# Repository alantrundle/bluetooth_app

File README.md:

# Project
* SwiftUI × CoreBluetooth Sample Code ...
# Built With
* CoreBluetooth
# Versioning
* target -> iOS 14.1 ↑
* Xcode --12.4
* Swift -- 5.3
* SwiftUI -- 2.0
# Authors
* Alan Trundle

# bluetooth_app
#

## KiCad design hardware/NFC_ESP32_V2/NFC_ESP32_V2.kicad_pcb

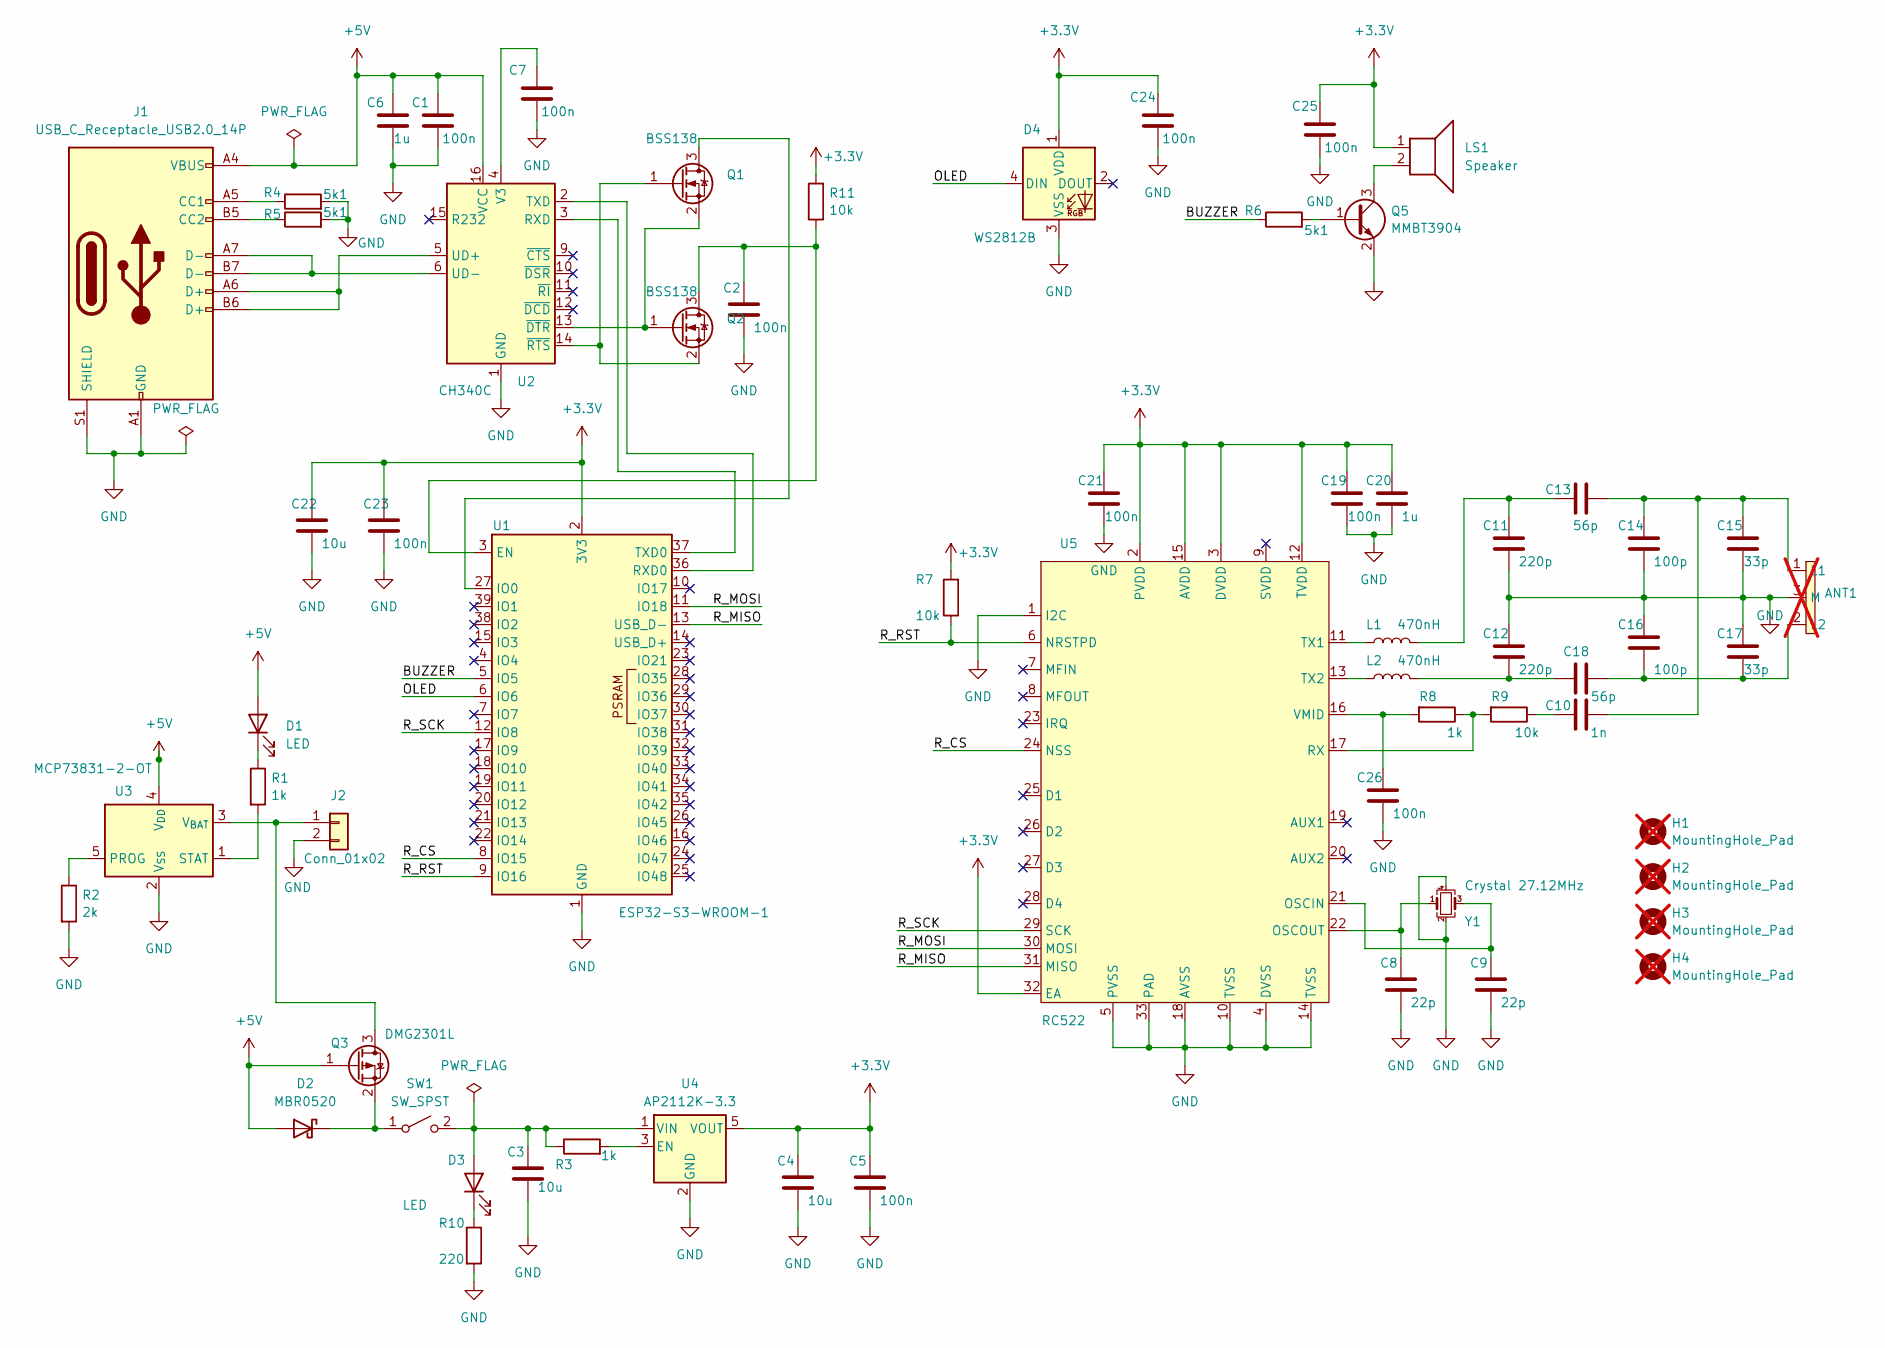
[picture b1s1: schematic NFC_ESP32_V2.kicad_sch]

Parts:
ANT1: RFID_Antenna2; not fitted
C1, C2, C5, C7, C19, C21, C23, C24, C25, C26: 100n; C_0603_1608Metric; LCSC C5137636
C3, C4, C22: 10u; C_0805_2012Metric_Pad1.18x1.45mm_HandSolder; LCSC C15850
C6, C20: 1u; C_0603_1608Metric; LCSC C1592
C8, C9: 22p; C_0603_1608Metric; LCSC C105620
C10: 1n; C_0603_1608Metric; LCSC C1523
C11, C12: 220p; C_0603_1608Metric
C13, C18: 56p; C_0603_1608Metric
C14, C16: 100p; C_0603_1608Metric
C15, C17: 33p; C_0603_1608Metric
D1, D3: LED; LED_0603_1608Metric
D2: MBR0520; D_SOD-123; LCSC C77335
D4: WS2812B; LED_WS2812B_PLCC4_5.0x5.0mm_P3.2mm; LCSC C114586
H1, H2, H3, H4: MountingHole_Pad; MountingHole_2.2mm_M2; not fitted
J1: USB_C_Receptacle_USB2.0_14P; USB_C_Receptacle_JAE_DX07S016JA1R1500; LCSC C3197885
J2: Conn_01x02; JST_ZH_S2B-ZR-SM4A-TF_1x02-1MP_P1.50mm_Horizontal; LCSC C20422588
L1, L2: 470nH; L_0603_1608Metric_Pad1.05x0.95mm_HandSolder; LCSC C280285
LS1: Speaker; Buzzer_TDK_PS1240P02BT_D12.2mm_H6.5mm; LCSC C76873
Q1, Q2: BSS138; SOT-23; LCSC C40912
Q3: DMG2301L; SOT-23; LCSC C7472914
Q5: MMBT3904; SOT-23; LCSC C2923360
R1, R3, R8: 1k; R_0603_1608Metric
R2: 2k; R_0603_1608Metric
R4, R5, R6: 5k1; R_0603_1608Metric
R7, R9, R11: 10k; R_0603_1608Metric
R10: 220; R_0603_1608Metric
SW1: SW_SPST; SW_Slide_SPDT_Angled_CK_OS102011MA1Q; LCSC C226259
U1: ESP32-S3-WROOM-1
U2: CH340C; SOIC-16_3.9x9.9mm_P1.27mm; LCSC C84681
U3: MCP73831-2-OT; SOT-23-5; LCSC C424093
U4: AP2112K-3.3; SOT-23-5; LCSC C51118
U5: RC522; HVQFN-32-1EP_5x5mm_P0.5mm_EP3.1x3.1mm_ThermalVias; LCSC C41361612
Y1: Crystal 27.12MHz; Crystal_SMD_3225-4Pin_3.2x2.5mm; LCSC C164053

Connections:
+3.3V: C4.1, C5.1, C19.1, C20.1, C21.1, C22.1, C23.1, C24.1, C25.1, D4.1 (VDD), LS1.1, R7.2, R11.2, U1.2 (3V3), U4.5 (VOUT), U5.2 (PVDD), U5.3 (DVDD), U5.12 (TVDD), U5.15 (AVDD), U5.32 (EA)
+5V: C1.1, C6.1, D1.2 (A), D2.2 (A), J1.A4 (VBUS), J1.A9 (VBUS), J1.B4 (VBUS), J1.B9 (VBUS), Q3.1 (G), U2.16 (VCC), U3.4 (V_{DD})
/BUZZER: R6.1, U1.5 (IO5)
/OLED: D4.4 (DIN), U1.6 (IO6)
/R_CS: U1.8 (IO15), U5.24 (NSS)
/R_MISO: U1.13 (USB_D-), U5.31 (MISO)
/R_MOSI: U1.11 (IO18), U5.30 (MOSI)
/R_RST: R7.1, U1.9 (IO16), U5.6 (NRSTPD)
/R_SCK: U1.12 (IO8), U5.29 (SCK)
GND: ANT1.3 (M), C1.2, C2.2, C3.2, C4.2, C5.2, C6.2, C7.2, C8.2, C9.2, C11.2, C12.1, C14.2, C15.2, C16.1, C17.1, C19.2, C20.2, C21.2, C22.2, C23.2, C24.2, C25.2, C26.2, D4.3 (VSS), J1.A1 (GND), J1.A12 (GND), J1.B1 (GND), J1.B12 (GND), J1.S1 (SHIELD), J2.2, Q5.2 (E), R2.2, R4.2, R5.2, R10.2, U1.1 (GND), U1.40 (GND), U1.41 (GND), U2.1 (GND), U3.2 (V_{SS}), U4.2 (GND), U5.1 (I2C), U5.4 (DVSS), U5.5 (PVSS), U5.10 (TVSS), U5.14 (TVSS), U5.18 (AVSS), U5.33 (PAD), Y1.2, Y1.4
unnamed: ANT1.1 (L1), C10.2, C13.2, C14.1, C15.1
unnamed: ANT1.2 (L2), C16.2, C17.2, C18.2
unnamed: C10.1, R9.1
unnamed: C11.1, C13.1, L1.2
unnamed: C12.2, C18.1, L2.2
unnamed: D1.1 (K), R1.1
unnamed: D2.1 (K), Q3.2 (S), SW1.1 (A)
unnamed: C3.1, D3.2 (A), R3.1, SW1.2 (B), U4.1 (VIN)
unnamed: D3.1 (K), R10.1
unnamed: J1.A5 (CC1), R4.1
unnamed: J1.B5 (CC2), R5.1
unnamed: J2.1, Q3.3 (D), U3.3 (V_{BAT})
unnamed: Q1.3 (D), U1.27 (IO0)
unnamed: Q1.1 (G), Q2.2 (S), U2.14 (~RTS)
unnamed: Q1.2 (S), Q2.1 (G), U2.13 (~DTR)
unnamed: C2.1, Q2.3 (D), R11.1, U1.3 (EN)
unnamed: Q5.1 (B), R6.2
unnamed: LS1.2, Q5.3 (C)
unnamed: U1.36 (RXD0), U2.2 (TXD)
unnamed: U1.37 (TXD0), U2.3 (RXD)
unnamed: J1.A6 (D+), J1.B6 (D+), U2.5 (UD+)
unnamed: J1.A7 (D-), J1.B7 (D-), U2.6 (UD-)
unnamed: C7.1, U2.4 (V3)
unnamed: R2.1, U3.5 (PROG)
unnamed: R1.2, U3.1 (STAT)
unnamed: R3.2, U4.3 (EN)
unnamed: C9.1, U5.21 (OSCIN), Y1.3
unnamed: C8.1, U5.22 (OSCOUT), Y1.1
unnamed: R8.1, R9.2, U5.17 (RX)
unnamed: L1.1, U5.11 (TX1)
unnamed: L2.1, U5.13 (TX2)
unnamed: C26.1, R8.2, U5.16 (VMID)

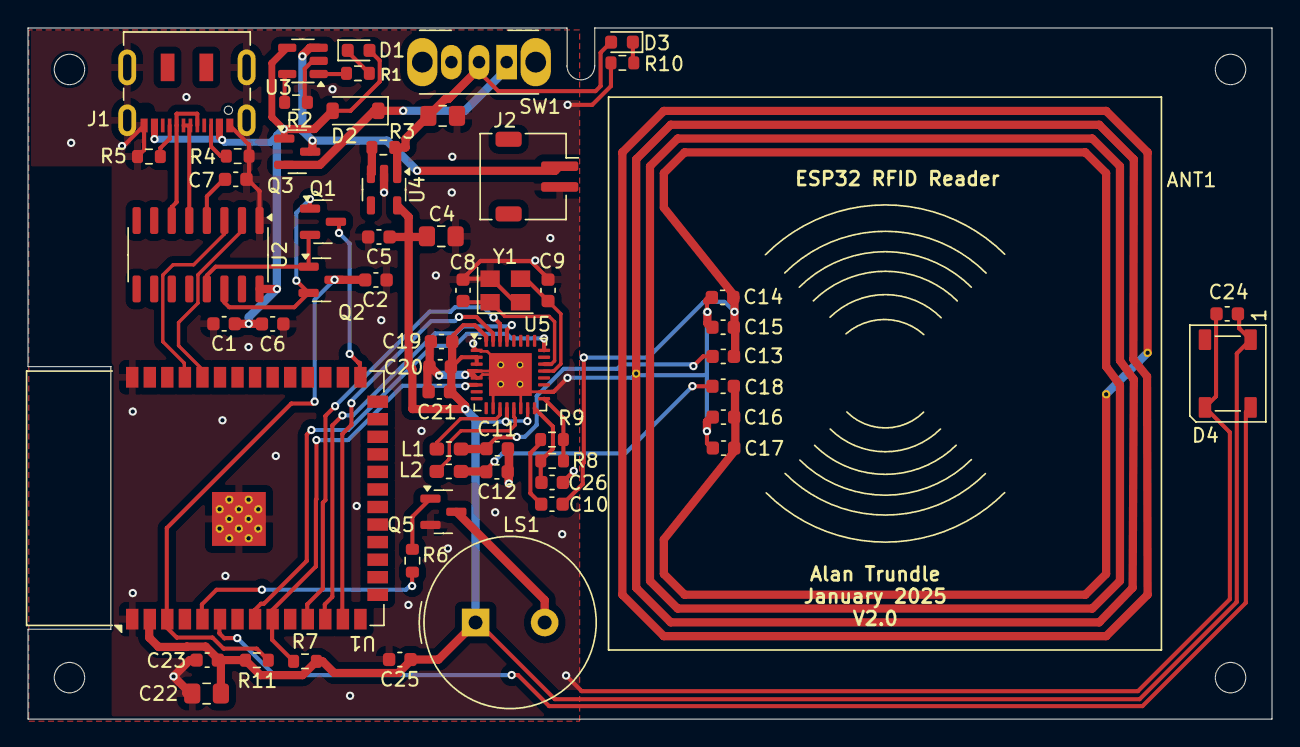
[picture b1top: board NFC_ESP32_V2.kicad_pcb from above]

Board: 2 copper layers, 90.0 x 50.0 mm, 62 parts (0 on the bottom side), 42 nets.

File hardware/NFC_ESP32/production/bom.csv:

Designator,Footprint,Quantity,Value,LCSC Part #
ANT1,RFID_Antenna2,1,~,
"C1, C19, C2, C21, C23, C24, C25, C26, C5, C7",0603,10,100n,C5137636
C10,0603,1,1n,	C1523
"C11, C12",0603,2,220p,
"C13, C18",0603,2,56p,
"C14, C16",0603,2,100p,
"C15, C17",0603,2,33p,
"C20, C6",0603,2,1u,C1592
"C22, C3, C4",0805,3,10u,C15850
"C8, C9",0603,2,22p,	C105620
"D1, D3",0603,2,LED,
D2,D_SOD-123,1,MBR0520,	C77335
D4,LED_WS2812B_PLCC4_5.0x5.0mm_P3.2mm,1,WS2812B,C114586
J1,USB_C_Receptacle_JAE_DX07S016JA1R1500,1,USB_C_Receptacle_USB2.0_14P,C3197885
J2,JST_ZH_S2B-ZR-SM4A-TF_1x02-1MP_P1.50mm_Horizontal,1,Conn_01x02,C20422588
"L1, L2",0603,2,470nH,	C280285
LS1,Buzzer_TDK_PS1240P02BT_D12.2mm_H6.5mm,1,Speaker,	C76873
"Q1, Q2",SOT-23,2,BSS138,C40912
Q3,SOT-23,1,DMG2301L,C7472914
Q5,SOT-23,1,MMBT3904,	C2923360
"R1, R3, R8",0603,3,1k,
R10,0603,1,220,
"R11, R7, R9",0603,3,10k,
R2,0603,1,2k,
"R4, R5, R6",0603,3,5k1,
SW1,SW_Slide_SPDT_Angled_CK_OS102011MA1Q,1,SW_SPST,C226259
U1,ESP32-WROOM-32D,1,ESP32-WROOM-32D,C6946015
U2,SOIC-16_3.9x9.9mm_P1.27mm,1,CH340C,C84681
U3,SOT-23-5,1,MCP73831-2-OT,C424093
U4,SOT-23-5,1,AP2112K-3.3,	C51118
U5,HVQFN-32-1EP_5x5mm_P0.5mm_EP3.1x3.1mm_ThermalVias,1,RC522,C41361612
Y1,Crystal_SMD_3225-4Pin_3.2x2.5mm,1,Crystal 27.12MHz,C164053

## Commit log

2024-11-04 second commit
2024-11-04 third comit
2024-11-04 Main
2024-11-05 Major DB changes
2024-11-06 View Changes to SecurityView
2024-11-16 Code changes
2024-11-30 Added kicad hardware files
2024-12-02 added fw
2024-12-02 upload
2024-12-02 updated updste.dat
2024-12-04 deleted old fw
2024-12-11 Added support for 4KB card
2024-12-16 ESP32 first commit
2024-12-20 Changed to resolve issues on Version 1.0
    Change RC522 symbol and fix crystal pins
    Swap D- and D+
    Move OLED and buzzer pins
    Power AVDD on RC522
2024-12-26 Added V2 Kicad directory and files
    Add NFC_ESP32_V2 directory an Kicad files.
    V2 Kicad updated to use ESP32 S3 in schematic and PCB
